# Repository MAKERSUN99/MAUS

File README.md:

# 🐭 MAUS
Arduino-Based Mouse Jiggler

MAUS is a compact Arduino-based device that simulates mouse movements to prevent screensavers and keep your computer active. Small, fun, and fully programmable, it also adds a splash of RGB flair to your workspace! ✨

---

## 📸 Gallery

<!-- Example animated GIF placeholder -->

---

## 🛒 Where to Buy

<p align="center">
  
</p>

<p align="center">
  
</p>

---

## 🔹 Overview

MAUS generates small, fake mouse movements (1 pixel up and down) to keep your computer active and disable screensavers.  
Perfect for automation without interaction and a little ambient light fun! 💡

---

## ⚙️ Features

- **MCU:** ATtiny85  
- **LEDs:** Red LED on PB0, WS2812B RGB LED on PB1  
- **Free pins:** PB2, PB3, PB4 (programmable)  
- **Default Fuse Settings:**  
  - **Lfuse:** 0xE1 – PLL Clock + Startup 64 ms  
  - **Hfuse:** 0xDD – External Reset pin enabled (Pin5 not usable as I/O) + BOD 2.7V + Enable Serial Program/Data Downloading  
  - **Efuse:** 0xFE – Self programming enabled  
- **Plug & Play:** Arduino firmware pre-installed  
- **PlatformIO support** with a custom MAUS board  

---

## 💻 Software

- Fully open-source Arduino code and KiCad schematics  
- Adafruit Neopixel Library required for RGB functionality  
- Micronucleus bootloader info: [Micronucleus GitHub](https://github.com/micronucleus/micronucleus)  
- Modify and customize the software to your needs  

---

## 📦 Installation & Usage

1. Plug MAUS into a USB port  
2. Observe the LED lights and simulated mouse movements  
3. Optional: Modify Arduino code for custom behaviors or RGB animations  

---

## 🔗 Links & Resources

- [GitHub Repository](https://github.com/MAKERSUN99/MAUS) – source code, schematics, firmware  
- [Tindie Store](https://www.tindie.com/stores/makersun/) – purchase MAUS  

---

## 🌟 Tagline

No more sleepy screens. No more endless logins.  
Just movement… with light.  
**MAUS: your silent digital sidekick.** 🖱️✨

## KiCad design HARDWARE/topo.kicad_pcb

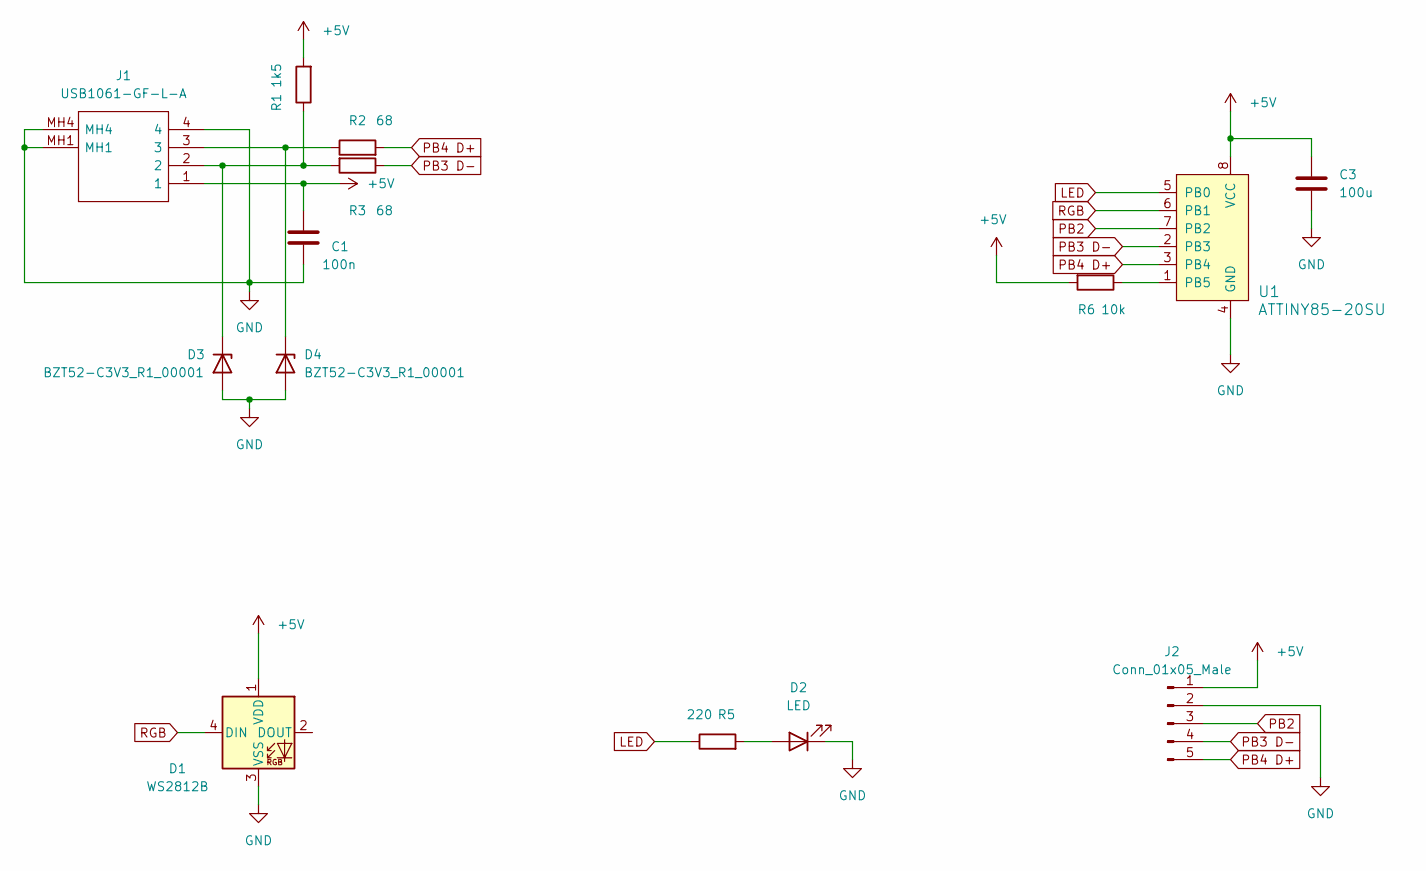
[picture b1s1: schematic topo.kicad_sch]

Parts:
C1: 100n; C_1206_3216Metric_Pad1.33x1.80mm_HandSolder
C3: 100u; C_1206_3216Metric_Pad1.33x1.80mm_HandSolder
D1: WS2812B; LED_WS2812B_PLCC4_5.0x5.0mm_P3.2mm
D2: LED; LED_1206_3216Metric_Pad1.42x1.75mm_HandSolder
D3, D4: BZT52-C3V3_R1_00001; D_SOD-123
J1: USB1061-GF-L-A; USB1061GFLA; Mouser Part Number 640-USB1061-GF-L-A
J2: Conn_01x05_Male; PinHeader_1x05_P1.27mm_Vertical
R1: 1k5; R_1206_3216Metric_Pad1.30x1.75mm_HandSolder
R2, R3: 68; R_1206_3216Metric_Pad1.30x1.75mm_HandSolder
R5: 220; R_1206_3216Metric_Pad1.30x1.75mm_HandSolder
R6: 10k; R_1206_3216Metric_Pad1.30x1.75mm_HandSolder
U1: ATTINY85-20SU; SOIC-8_W5.6mm_MOD; MPN ATTINY85-20SU; Digi-Key_PN ATTINY85-20SU-ND

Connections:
+5V: C1.1, C3.1, D1.1 (VDD), J1.1, J2.1, R1.2, R6.2, U1.8 (VCC)
GND: C1.2, C3.2, D1.3 (VSS), D2.1 (K), D3.2 (A), D4.2 (A), J1.4, J1.MH1, J1.MH4, J2.2, U1.4 (GND)
LED: R5.1, U1.5 (PB0)
unnamed: D2.2 (A), R5.2
unnamed: D3.1 (K), J1.2, R1.1, R3.2
unnamed: D4.1 (K), J1.3, R2.1
unnamed: R6.1, U1.1 (PB5)
PB2: J2.3, U1.7 (PB2)
PB3 D-: J2.4, R3.1, U1.2 (PB3)
PB4 D+: J2.5, R2.2, U1.3 (PB4)
RGB: D1.4 (DIN), U1.6 (PB1)

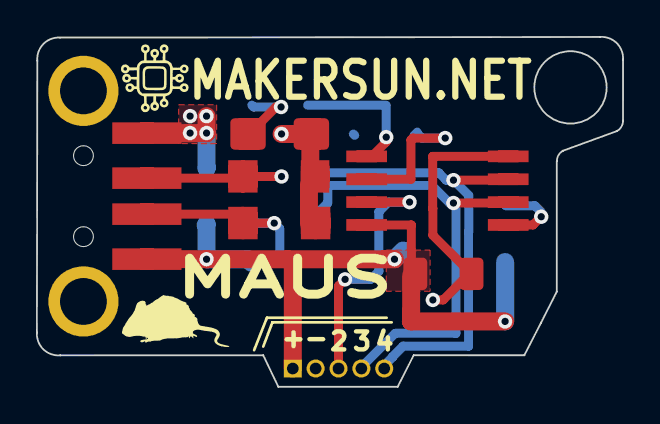
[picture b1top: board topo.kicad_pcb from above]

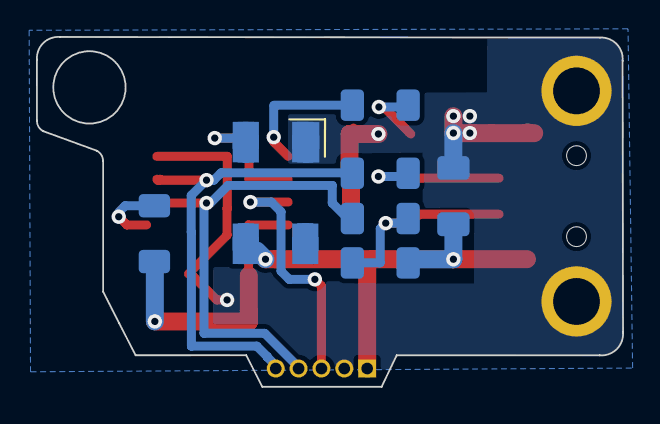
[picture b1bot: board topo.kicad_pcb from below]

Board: 2 copper layers, 32.6 x 19.4 mm, 14 parts (7 on the bottom side), 11 nets.

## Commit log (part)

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2023-03-09 Create a
2023-03-17 Rename package_digistump_index.json to package_MAUS_index.json
2023-10-25 MANUALE IN ITALIANO
2023-10-25 Manuals for ARDUINO IDE V2.2.1
2024-03-05 Update README.md
    add ebay link
2024-09-27 Create maus_V3_TaskScheduler
    new approach with TaskScheduler
2024-09-27 Rename maus_V3_TaskScheduler to maus_V3_TaskScheduler.ino
2025-12-13 Revamp README with new sections and formatting
    Updated README to enhance clarity and structure, added sections for gallery, features, software, installation, and resources.
